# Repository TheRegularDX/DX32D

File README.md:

# DX32D Dingus 
Dongle-type custom ESP32S3 development board, designed to be "plug-n-play"

## PlatformIO support
just like the DX32A, this board has plattformio support. instructions and json file are [here](https://github.com/TheRegularDX/DX32A).

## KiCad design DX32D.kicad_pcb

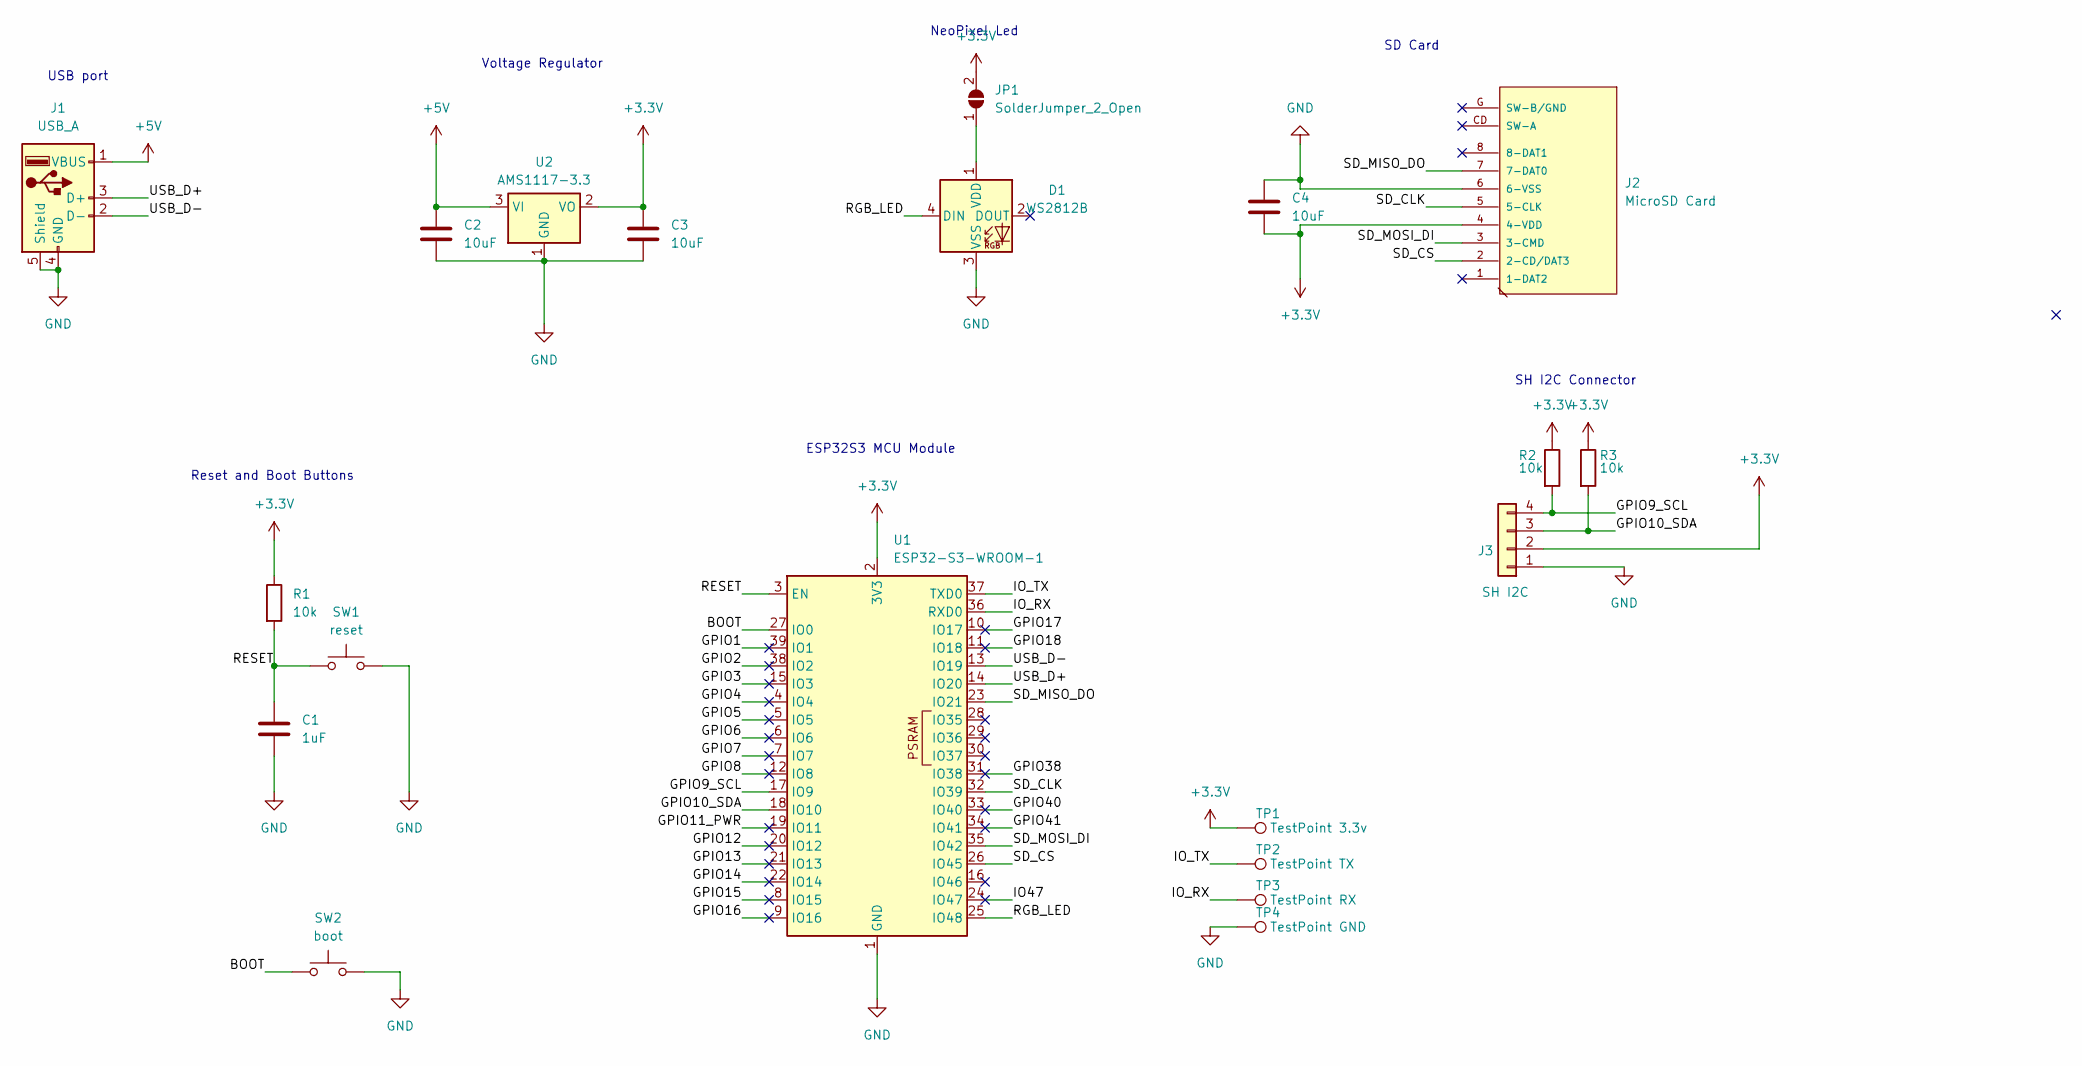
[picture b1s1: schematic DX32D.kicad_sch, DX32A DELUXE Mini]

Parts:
C1: 1uF; C_0805_2012Metric_Pad1.18x1.45mm_HandSolder
C2, C3, C4: 10uF; C_0805_2012Metric_Pad1.18x1.45mm_HandSolder
D1: WS2812B; LED_WS2812B_PLCC4_5.0x5.0mm_P3.2mm
J1: USB_A; USB_A_CNCTech_1001-011-01101_Horizontal
J2: MicroSD Card; 112J-TDAR-R01
J3: SH I2C; JST_SH_SM04B-SRSS-TB_1x04-1MP_P1.00mm_Horizontal
JP1: SolderJumper_2_Open; SolderJumper-2_P1.3mm_Open_TrianglePad1.0x1.5mm
R1, R2, R3: 10k; R_0805_2012Metric_Pad1.20x1.40mm_HandSolder
SW1: reset; SW_Push_SPST_NO_Alps_SKRK
SW2: boot; SW_Push_SPST_NO_Alps_SKRK
TP1: TestPoint 3.3v; TestPoint_Pad_1.0x1.0mm
TP2: TestPoint TX; TestPoint_Pad_1.0x1.0mm
TP3: TestPoint RX; TestPoint_Pad_1.0x1.0mm
TP4: TestPoint GND; TestPoint_Pad_1.0x1.0mm
U1: ESP32-S3-WROOM-1
U2: AMS1117-3.3; SOT-223-3_TabPin2

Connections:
+3.3V: C3.1, C4.2, J2.4 (4-VDD), J3.2, JP1.2 (B), R1.1, R2.1, R3.1, TP1.1, U1.2 (3V3), U2.2 (VO)
+5V: C2.1, J1.1 (VBUS), U2.3 (VI)
/BOOT: SW2.1, U1.27 (IO0)
/GPIO1: U1.39 (IO1)
/GPIO2: U1.38 (IO2)
/GPIO3: U1.15 (IO3)
/GPIO4: U1.4 (IO4)
/GPIO5: U1.5 (IO5)
/GPIO6: U1.6 (IO6)
/GPIO7: U1.7 (IO7)
/GPIO8: U1.12 (IO8)
/GPIO9_SCL: J3.4, R2.2, U1.17 (IO9)
/GPIO10_SDA: J3.3, R3.2, U1.18 (IO10)
/GPIO11_PWR: U1.19 (IO11)
/GPIO12: U1.20 (IO12)
/GPIO13: U1.21 (IO13)
/GPIO14: U1.22 (IO14)
/GPIO15: U1.8 (IO15)
/GPIO16: U1.9 (IO16)
/GPIO17: U1.10 (IO17)
/GPIO18: U1.11 (IO18)
/GPIO38: U1.31 (IO38)
/GPIO40: U1.33 (IO40)
/GPIO41: U1.34 (IO41)
/IO47: U1.24 (IO47)
/IO_RX: TP3.1, U1.36 (RXD0)
/IO_TX: TP2.1, U1.37 (TXD0)
/RESET: C1.1, R1.2, SW1.1, U1.3 (EN)
/RGB_LED: D1.4 (DIN), U1.25 (IO48)
/SD_CLK: J2.5 (5-CLK), U1.32 (IO39)
/SD_CS: J2.2 (2-CD/DAT3), U1.26 (IO45)
/SD_MISO_DO: J2.7 (7-DAT0), U1.23 (IO21)
/SD_MOSI_DI: J2.3 (3-CMD), U1.35 (IO42)
/USB_D+: J1.3 (D+), U1.14 (IO20)
/USB_D-: J1.2 (D-), U1.13 (IO19)
GND: C1.2, C2.2, C3.2, C4.1, D1.3 (VSS), J1.4 (GND), J1.5 (Shield), J2.6 (6-VSS), J3.1, SW1.2, SW2.2, TP4.1, U1.1 (GND), U1.40 (GND), U1.41 (GND), U2.1 (GND)
unnamed: D1.1 (VDD), JP1.1 (A)

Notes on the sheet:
ESP32S3 MCU Module
Voltage Regulator
SD Card
SH I2C Connector
USB port
NeoPixel Led
Reset and Boot Buttons

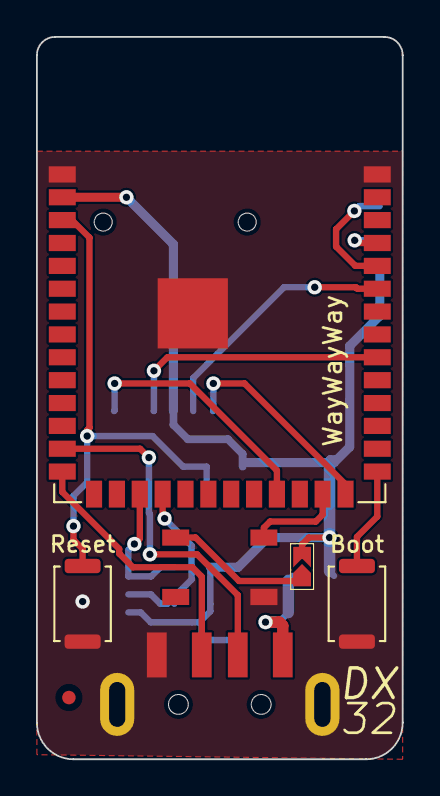
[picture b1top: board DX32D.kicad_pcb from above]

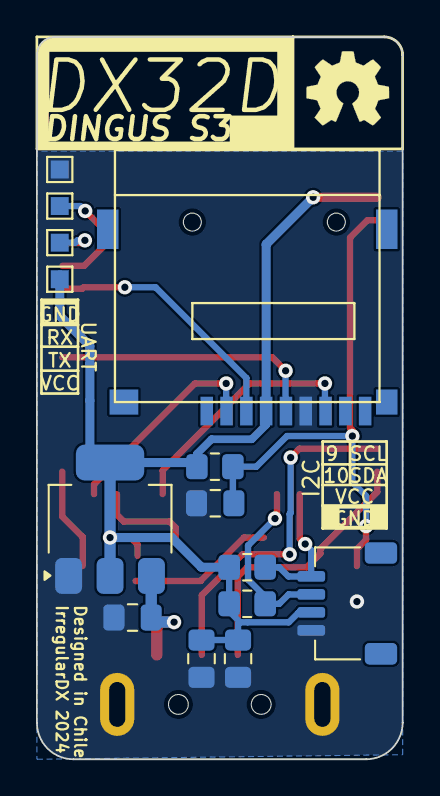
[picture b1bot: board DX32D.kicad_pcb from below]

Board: 2 copper layers, 20.3 x 40.1 mm, 21 parts (14 on the bottom side), 17 nets.

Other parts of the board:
Fiducial: Fiducial_0.75mm_Mask1.5mm

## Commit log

2024-04-02 made some small changes
2024-04-02 Create LICENSE
2024-04-04 updated board
    changed the width of the power pads.... i should have just set a rule instead
